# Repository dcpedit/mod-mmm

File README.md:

# Mod Mmm PCB for the IBM Model M

This project is designed to replace all internal compoents of an IBM Model M keyboard.  Only the curved steel backplate is needed for the PCB to be mounted on.

Typing test video: https://youtu.be/QOiLOHnEyzo

Image gallery: https://imgur.com/a/R9mSC4u

## Features

* Hotswap PCB for MX switches
* Multiple layout support, including ISO, split spacebar, and 4x5 numpad. [KLE link](http://www.keyboard-layout-editor.com/#/gists/e5cd226119123328166c9ac3b0ec58fc)
* PCB mount stabalizers
* Under-switch LED for caps, scroll, and num lock
* Supports up to 3 rotary encoders
* Piezo buzzer
* Solenoid
* USB-C support via STM32F411 Blackpill.
* Bluetooth support via PillBug.
* Vial firmware
* ZMK firmware (for BT PillBug)

## Ortholinear Edition

There is a separate PCB that supports ortholinear layout.  Details are located here:  [Ortholinear Edition](pcb-ortho)

## The Build "Stack"

The following is a table of measurements of everything that's stacked on top of the steel backplate.  The key spacing was taken from hires scans I made of the Model M's wiring membrane.  I recalculated the spacing for each decrease in radius except for the foam where I reused the numbers from the switch plate.  I was lazy and figured foam can stretch anyways.

| Part            | Thickness (mm) | Radius (mm) | Radius Start | 1u vertical spacing (mm) |
|-----------------|----------------|-------------|--------------|--------------------------|
| Steel backplate | 1.0            | 276.635     | inner        | 20.617
| Hex Standoffs   | 4.0            | n/a         | n/a          | n/a
| Mod Mmm PCB     | 1.0            | 272.135     | center       | 20.560
| Plate Foam      | 3.5            | n/a         | n/a          | n/a
| Switch Plate    | 1.5            | 267.385     | center       | 20.201

## Parts List

| Part                        | Count | Notes |
|-----------------------------|-------|-------|
| Mod Mmm PCB                 | 1     | 1mm FR4 thickness
| Mod Mmm Daughterboard       | 1     | 1.2mm FR4 thickness
| Blackpill (STM32F411)       | 1     |
| M2.5x3mm Wafer Screw        | 116   | [Link](https://www.aliexpress.us/item/2255800885711092.html?spm=a2g0o.order_list.order_list_main.22.1875180223MOsy&gatewayAdapt=glo2usa&_randl_shipto=US)
| M2.5x4mm Hex Standoff       | 58    | [Link](https://www.aliexpress.us/item/2251832790997097.html?spm=a2g0o.order_list.order_list_main.23.1875180223MOsy&gatewayAdapt=glo2usa&_randl_shipto=US)
| M2.5x5.5 Insulated Washer   | 58    | Probably not needed (step 8).  [Link](https://www.aliexpress.us/item/2255801049052739.html?spm=a2g0o.order_list.order_list_main.24.1875180223MOsy&gatewayAdapt=glo2usa&_randl_shipto=US)
| BAV70 Diodoe                | 55    | [Link](https://www.mouser.com/ProductDetail/Nexperia/BAV70215?qs=me8TqzrmIYX%252B%2FJ6jIjzNeA%3D%3D&countrycode=US&currencycode=USD)
| Piezo Buzzer                | 1     | [Link](https://www.digikey.com/en/products/detail/tdk-corporation/PS1240P02BT/935924)
| 5v Solenoid                 | 1     | [Link](https://www.digikey.com/en/products/detail/sparkfun-electronics/ROB-11015/6163694)
| Kailh Hotswap Sockets       | 101   | More needed if non-ANSI layout
| FFC Cable (30 pos/1mm pitch)| 1     | Cable length: 30 inches [Link](https://www.digikey.com/en/products/detail/molex/0151670470/3281723)
| FFC Connector (30 pos/1mm)  | 2     | [Link](https://www.digikey.com/en/products/detail/omron-electronics-inc-emc-div/XF3M-1-3015-1B/4331813)
| 3mm LED (green)             | 3     | For status panel. [Link](https://www.digikey.com/en/products/detail/w%C3%BCrth-elektronik/151031VS06000/4489988)
| 2mm LED (white)             | 3     | For keycap status. [Link](https://www.amazon.com/gp/product/B01C5HL0PO/ref=ppx_yo_dt_b_search_asin_title?ie=UTF8&th=1)
| 470Ω Resistor               | 3     | For panel LED |
| 10kΩ Resistor               | 3     | For keycap LED |
| 22kΩ Resistor               | 1     | Pullup for pin A10 |
| TIP120 Transistor           | 1     | For solenoid. [Link](https://www.amazon.com/gp/product/B08212F42Z/ref=ppx_yo_dt_b_search_asin_title?ie=UTF8&psc=1)
| 1N4001 Diode                | 1     | For solenoid. Comes with above kit |
| 2.2kΩ Resistor              | 1     | For solenoid. Comes with above kit |
| Mill-Max 310 sockets (1x20) | 2     |
| Mill-Max 310 sockets (1x4)  | 1     |
| Mill-Max round pin (¼in)    | 44    | [Link](https://www.mouser.com/ProductDetail/Mill-Max/3320-0-00-15-00-00-03-0?qs=s8Nb1z4Wn%2FQ16WBIwCPrTw%3D%3D&countryCode=US&currencyCode=USD)
| 2u plate mount stabalizer   | 7     | Count varies based on layout
| 7u plate mount stabalizer   | 1     | For 7u spacebar
| EC11 Rotary Encoder         | 3     | Optional [Link](https://www.mouser.com/ProductDetail/Bourns/PEC12R-4222F-S0024?qs=%252B9%2Fcbd0IE0SDcVz9RehHSg%3D%3D)
| Rotary Encoder Knob (17mm)  | 3     | Optional [Link](https://www.amazon.com/dp/B07K8589MJ?ref=ppx_yo2ov_dt_b_product_details&th=1)
| Switch plate (9 piece set)  | 1     | Optional 1.5mm acrylic
| Case foam (under PCB)       | 1     | Optional 2mm EVA
| Plate Foam                  | 1     | Optional 3.5mm EVA foam (or 2mm + [1.5mm](https://www.aliexpress.us/item/3256804208838525.html?spm=a2g0o.order_list.order_list_main.5.21ef1802FA7EIC&gatewayAdapt=glo2usa&_randl_shipto=US))

For the Mill-Max 310 series low profile sockets, I found it more cost efficient to just buy a really long socket and cut the sizes I need with flush cutters.  [Here's an example of a 1x64 socket.](https://www.mouser.com/ProductDetail/Mill-Max/310-93-164-41-001000).  The only thing is that the edges are rough after the cut, but it doesn't bother me.

You can probably use others ways to mount the Blackpill.  Just make sure that final height of the USB port is somewhat centered inside the case port.

## PCB Build Guild

To complete this build, you will need to get the main PCB and daughterboard manufactured.  The main PCB will need to be **1mm thick FR4**, and I made the daughterboard 1.2mm to match the thickness of the original one that came with the keyboard.  I personally like using [JLCPCB](https://jlcpcb.com/), so I've included a `zip` file in the each respective directory that you can upload to their service if you decide to go with them.  (FYI, you will need to order a minimum of 5 boards each).

### 1) Disassembly
The first step is to disassemble your Model M and clean it if neccessary.  There are lots of tutorials online on how to do this, and make sure you have a 7/32 inch (5.5mm) socket for the case screws.  I followed this one from YouTube: https://youtu.be/VsIr8dl_7Kk.

The hardest part is removing the plastic rivets that holds the frame assembly against the steel backplate.  I used a razor blade with a few pieces of electrical tape wrapped around the back for better grip and for safety (to easily tell which is the sharp side).  I would then rock the blade around a rivet in a "see-saw" motion while putting pressure on the blade until it popped off.  It'd be a good idea to place some type of "backstop" like tall box to prevent the rivets from flying everywhere.

### 2) Shape PCB

Using the hex standoffs and a few screws, mount the PCB onto the steel backplate for 24hrs.  You only need enough screws & standoffs for the PCB to hold its shape.  After you remove the PCB, you want there to be a slight curve to the FR4 before soldering on the components.  This way, the componenets and solder joints experience less stress when the PCB is bent into its final shape.

### 2) BAV70 Diodes

Flip the PCB over to the backside and solder on the BAV70 diodes (D1 - D55). Place a dab of solder on the single bottom pad of the diode on the PCB. Then using tweesers, position the diode so that the legs line up with the pads. Then using the point of one tweeser leg, gently hold the top of the diode in place while melting the dab of solder that was placed on the bottom pad previously. With the diode now held in position, solder the top two legs to their respective pads.

### 3) Kailh Hotswap Sockets & Rotary Encoders

Place some solder on one of the hot swap socket pads. There should be enough solder to make a small mound. Place the socket into position and melt the mound of solder that was previously added while pressing down on the center of the socket. Be sure to avoid touching any metalic parts to prevent burns. Keep the soldering iron on the pad long enough for the solder to flow around the socket connector (usually around 3 to 4 seconds). Now solder the other socket connector to the pad.

You can replace any of the keys in the Print Screen cluster with a rotary encoder.  Just make sure you don't place a hotswap socket there, and solder in the EC11 encoder instead.

Also realized the logo on the back is way too busy.  I've changed it to be a small logo on the front in v2, which is the current repo version.

### 4) Status Panel LEDs and resistors

These three LEDs go under the status panel (NUM1, CAP1, and SCRL1).  The short pin of the LED goes in the square pad.  As for the accompanying 470Ω resistors (R4, R5, and R6), orientation does not matter.  The LEDs here can be soldered in with extra height so that they sit closer to the "window" cutout on the case.  I mesaured the space between the PCB and the window to be 10mm.

### 5) Switch LEDs and resistors (optional)

These LEDs go under the caps lock, scroll lock, num lock switches.  Depending on your switch, you may have to solder these in AFTER placing the switch into the socket.  You can tell by looking under the switch to see if there's a hole big enough for the LED to fit through.  If there are only 2 small holes for the LED pins, then the switch needs to go in first.  The short pin of the LED goes in the square pad.  As for the accompanying 10kΩ resistors (R1, R2, and R3), orientation does not matter.

I use a higher resistance here for the white LEDs because they tend to be too bright for me personally.  Feel free to lower the resistance if you want them brighter, or if you choose a different color.

### 6) Stabalizers

Install your stabalizers of choice onto the PCB.  For the vertical stabs, in order to counteract the curvature of the PCB, I used adhesive stabalizer pads and cut them in half lengthwise (band-aids would work as well).  I then placed them on the inside half of where the stabs would sit.  The idea here is to angle the stabs back outwards so that they remain parallel.

Note that I made all the stab holes a tad larger in the vertical direction to allow for some wiggle room.

### 7) FFC Connector

This can be a bit tricky to hand solder, so take it slow, and use plenty of flux.  Place a dab of solder on one of the large pads on the side.  Position the connector on top of the pads making sure that the small pins are centered relative to their respective pads.  While holding the connector in place, melt the dab of solder that was placed earlier so that the one side is held in place.  Now solder the other end of the connector so that it's held in position.  Moving on to the the small pins, I initally tried "drag soldering", but I ended up bridging a lot of pins.  If this happens, just clean it up with some solder wick.

I found that the better way to do this is to pull out the sharpest tip you have for your soldering iron, and placing a tiny dab of solder on each pad, while avoiding touching the adjacent pins with the iron tip.  Again, make sure you use plenty of flux.  This way, the solder will simply flow around the pin without bridging the neighboring pins.

There's probably other connectors out there that can do the same job at a cheaper price.  I'm not an expert on FFC components, so all suggestions are welcome.  (Same thing for the FFC cable)

### 8) Install PCB standoffs

Starting with the steel backplate, insert a screw from the back and screw a standoff on from the other side.  Keep it loose enough so that the standoff can rattle around a bit.  Do this for all the mount holes on the steel plate, even if you end up not using them because they're still good for support.  Make note of the holes that are left open in my photo above (circled red) and do the same to prevent interference with the case/components. You should also put a standoff in corner top-right hole beneath the plastic post (circled green) for added support.

Slip the steel backplate back into the bottom of the case.  You'll need to slide the bottom into the slots first, and then place the plastic case posts into the top-left and top-right corners of the steel backplate.

### 9) Case foam (optional)

If you opted for the 2mm EVA case foam, you'll need to place it over the steel plate before installing the PCB.  The holes in the foam should line up over the standoffs. (Filename: `pcb/case-foam.ai`)

### 10) Center and Install PCB

Line up the PCB over the holes and place 2 or 3 screws positioned horizontally from each other near the center of the PCB.  Push the center firmly down onto the standoffs to force the PCB to bend (this part is a bit nerve racking, especialy when you hear creaking noises), and secure it with the screws while holding it in place.

Now place a switch and keycap combo at the corner of every section of the keyboard (ex: Esc, F1, ~, Ctrl, Print, Num-Lock, Num-Enter, etc).  Put the top of the Model-M case on, making sure it's aligned and fully seated with no gaps.  Carefully shift the PCB around slightly to get the keycaps to be in the correct position with equal amounts of spacing from the keycap to the case walls.  Basically you're trying to center the PCB by eye-balling the keycap gaps.

With the PCB now centered, remove the top of the case and begin screwing in all the mounting screws.  I'd suggest starting near the center and spiral outwards towards the edges.  This is where you'll probably need to shift the loose standoffs around to line the holes up.  Also, if you run into the problem where the top and bottom screws bump into each other inside the standoff, you'll need to add an insulated washer to the bottom screw.  Place the top case back on every once in a while to make sure the PCB didn't shift and is still centered.  After you're done, remove the steel backplate from the bottom of the case and tighten all the screws on the back.  If you feel that the standoffs are just spinning while you're turning the screw, just squeeze the PCB and backplate together so that it pinches the standoff and keeps it from spinning.

NOTE:  I noticed that the vertical 2u stabs in the numpad were blocking some of the screw holes in rev 1 of the PCB.  I flipped the stabs in rev 2 which is the version in the repo.

## Daughterboard Build Guide

### a) Solenoid Components
Bend the narrow part of the pins on the TIP120 back towards the heatsink at a 90 degree angle.  Solder it into place.

The 2.2k resistor goes into the R2.2 spot (orientation does not matter).  The 1N4001 diode goes in to the 1N4001 position where the line matches the printed line on the board.  The solenoid wires don't have an orientation, and you can solder them directly into the holes or use a header/connector.

### b) 22k Pullup Resistor

In order to use pin A10 on the Blackpill, a 22k pullup resistor is needed (according to the [QMK docs](https://docs.qmk.fm/#/platformdev_blackpill_f4x1)). Solder this into the R1 position.  Orientation does not matter.

### c) Blackpill Development Board

It's probably best to flash the firmware onto the Blackpill first using the `bin` file in the `firmware` directory. Hook it up to [QMK Toolbox](https://github.com/qmk/qmk_toolbox/releases) and push the following buttons to place it in bootloader mode before flashing:
* Press and hold the BOOT0 button
* Press and release NRST (reset) button
* Release BOOT0 button

Solder the Mill-Max 310 sockets onto the daughterboard.  Then place a piece of masking tape over the pin holes, and insert each pin though the tape and into its hole with tweezers.  Then set the Blackpill into place with the components facing up and the USB port facing the top of the daughterboard.  Solder the pins into place, and then carefully and slowly remove the Blackpill.  If you pull too fast and hard, one edge will suddenly pop loose, bending the pins on the opposite side.  Remove the masking tape, and push the Blackpill back into place.

Lazy-man's short cut: skip the masking tape.  But note that using too much solder will cause it to flow down the pin and into the socket.  If this happens, the keyboard will still work, but you won't be able to remove the Blackpill without desoldering.

### d) Piezo Buzzer

Solder this into the BZ1 position.  Orientation does not matter.

### e) Assembly

Remove the steel backplate from the case if you haven't already.  If you have a Model M that came with a smaller PCB, you will need to clip away the plastic bracket to make room for the larger footprint of the daughterboard.  Make sure the clamp on the FFC connector is lifted up, insert the FFC cable, and press the clamp back down.  Place the daughterboard into position inside the case bottom.  I don't have a good way to secure it to the case (I'm reluctant to drill holes), so a piece of tape or double-sided adhesive foam will do for now.

Put the steel backplate with mounted PCB back into place, and connect the other end of the FFC cable to the main board.  At this point, you can install your switches and keycaps, screw the case back together, and be done!

BUT, after some testing, I noticed that my Kailh Box White switches were not very stable.  This is probably due to the fact they they were 3 pin switches instead of 5, and the hot swap sockets didn't grip the switch pins that tightly.  This is why I opted to make a switch plate to better hold the switches in place.  This also meant I had to cut 3.5mm thick foam (technically 2mm + 1.5mm) to act as a spacer between the PCB and the switch plate.

Unfortunately, there was not enough room in the case to house a single switch plate that spanned the entire board, so I had to break the plate up into smaller sections (9 total), which ended up working pretty well.  The Esc key had its own little 1u switch plate, so the stability still wasn't great, but it'll have to do.  I also messed up the foam spacing for the top row, so I had to cut it off as a separate piece.  This is fixed in the repo version, which is in the `case/plate-ansi_v2.ai`.  Plates for other layouts need to be created.

### f) F-row Plate support 

During my testing, I found that the F row keys (especially the ESC key) were not very stable due to the switch plate being only 1u in height. To fix this, I decied to remove the 1.5mm foam under these keys, and replace it with a long strip of 1.5mm acrylic. I then used acrylic cement to glue the small switch plates to this strip, giving the entire top row some much needed support.

The layer in the plate file should be labeled `F-row support`.

The easiest way to apply the acrylic cement (I use Weld-On #4) is to mount lay the 2mm foam down on top of the PCB, place the F-row support strip on top, the small switch plates on top of that, and finally install some switches to hold everything in place. Then using your needle tip applicator, run it along the top edge between the switch plate and support while using gravity to pull the cement into the gap. Then tilt your keyboard back so that the bottom edge is up, and do the same thing along the bottom edge, again using gravity to pull the cement into the gap.

## Inspiration

Thanks to all the project/product creators who have inspired the creation of the Model Mmm:

* [Model-H](https://modelh.club/): Open source USB controller for the Model M
* [Class 80](https://geekhack.org/index.php?topic=118401.0) by [MMStudio](https://mmkeys.com/): Premium TKL retro-styled board with a solenoid and buzzer
* [Command 65](https://geekhack.org/index.php?topic=117715.0) by [Play Keyboard](https://www.play-keyboard.store/): Retro-styled wireless keyboard with buzzer based off the Commodore 64

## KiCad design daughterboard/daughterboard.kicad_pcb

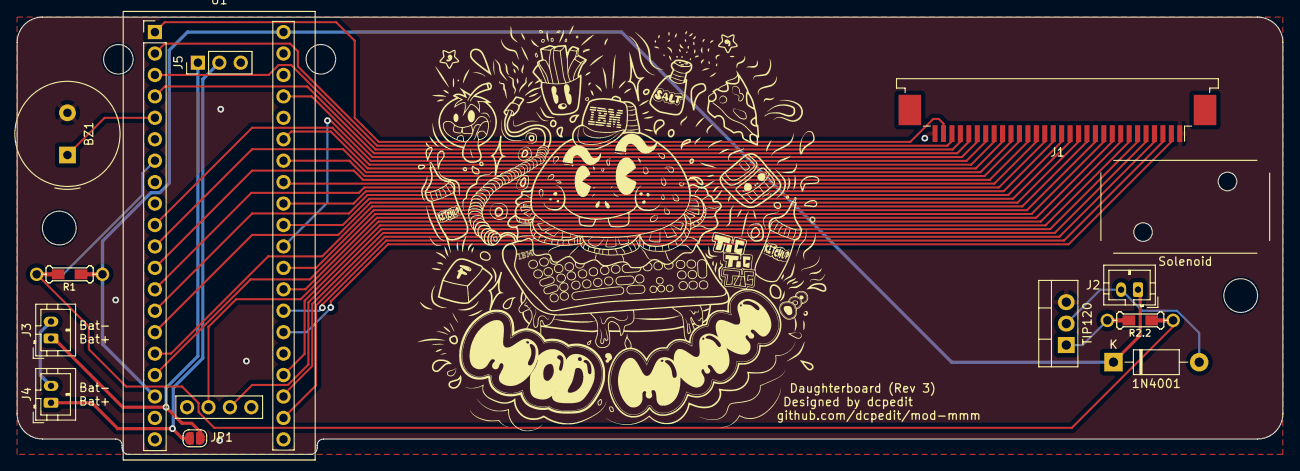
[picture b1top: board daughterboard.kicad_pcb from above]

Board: 2 copper layers, 150.0 x 51.8 mm, 14 parts (0 on the bottom side), 37 nets.

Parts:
1N4001: 1N4001; D_DO-41_SOD81_P10.16mm_Horizontal
BZ1: Buzzer; Buzzer_TDK_PS1240P02BT_D12.2mm_H6.5mm
J1: Conn_01x30; USB_B_OST_USB-B1HSxx_Horizontal
J1#2: Conn_01x30; TE_3-84952-0_1x30-1MP_P1.0mm_Horizontal
J2: Conn_sol; JST_PH_B2B-PH-K_1x02_P2.00mm_Vertical
J3: Bat_in; JST_PH_B2B-PH-K_1x02_P2.00mm_Vertical
J4: Bat_out; JST_PH_B2B-PH-K_1x02_P2.00mm_Vertical
J5: PWR_switch; PinHeader_1x03_P2.54mm_Vertical
JP1: Switch_bypass; SolderJumper-2_P1.3mm_Open_RoundedPad1.0x1.5mm
R1: R_22K; Resistor-Hybrid
R2.2: R_2.2; Resistor-Hybrid
Solenoid: solenoid
TIP120: TIP120; TO-220-3_Vertical
U1: YAAJ_WeAct_BlackPill_Part_Like_SWD_Breakout; YAAJ_WeAct_BlackPill_SWD_2

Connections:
+5V: 1N4001.1 (K), J2.1, R1.1, U1.18 (5V), U1.40 (5V)
BAT_B: J3.2, J4.2
BAT_R: J3.1, J5.1, JP1.1 (A)
BAT_RR: J4.1, J5.2, JP1.2 (B)
BUZ: BZ1.1 (-), U1.5 (PA8)
CAPS_LED: J1#2.29, U1.1 (PB12)
COL0: J1#2.28, U1.2 (PB13)
COL1: J1#2.27, U1.3 (PB14)
COL2: J1#2.26, U1.4 (PB15)
COL3: J1#2.23, U1.10 (PA15)
COL4: J1#2.22, U1.35 (PB1)
COL5: J1#2.11, U1.29 (PA3)
COL6: J1#2.10, U1.17 (PB9)
COL7: J1#2.7, U1.24 (PC15)
COL8: J1#2.5, U1.23 (PC14)
COL9: J1#2.4, U1.22 (PC13)
GND: BZ1.2 (+), J1#2.1, J1#2.30, TIP120.3 (E), U1.19 (GND), U1.39 (GND)
NUM_LED: J1#2.3, U1.27 (PA1)
unnamed: 1N4001.2 (A), J2.2, TIP120.2 (C)
unnamed: R2.2.2, TIP120.1 (B)
RE1: J1#2.9, U1.28 (PA2)
RE2: J1#2.8, U1.43 (SWIO)
RE3: J1#2.6, U1.42 (SWCLK)
ROW0: J1#2.25, U1.37 (PB10)
ROW1: J1#2.21, U1.11 (PB3)
ROW2: J1#2.20, U1.34 (PB0)
ROW3: J1#2.19, U1.12 (PB4)
ROW4: J1#2.18, U1.33 (PA7)
ROW5: J1#2.17, U1.13 (PB5)
ROW6: J1#2.24, U1.30 (PA4)
ROW7: J1#2.16, U1.32 (PA6)
ROW8: J1#2.15, U1.14 (PB6)
ROW9: J1#2.14, U1.31 (PA5)
ROW10: J1#2.13, U1.15 (PB7)
ROW11: J1#2.12, U1.16 (PB8)
SCRL_LED: J1#2.2, U1.26 (PA0)
SOL: R1.2, R2.2.1, U1.7 (PA10)

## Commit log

2023-03-18 Daughterboard
2023-03-21 Daughterboard updates
2023-04-07 daughterboard rewire
2023-04-11 Plate design
2023-04-14 Add images
2023-04-15 Add firmware
2023-04-16 Update PCB silkscreen
2023-04-17 Move dev files to dev branch
2023-04-17 Fix alignment
2023-04-17 Moved dev files
2023-04-17 Note about plate screws
2023-04-19 Fix broken traces
2023-08-28 Add case foam, split plates, and NES badge
2023-08-28 Update readmes
2023-11-19 v3 with 10u support
2024-04-13 Fix ortho diode
2024-04-23 Fix incorrect mill max part #
2024-05-30 Add ortho readme and firmware
2024-05-31 Move firmware
2024-05-31 Remove exports
2024-05-31 Fix pcb thickness
